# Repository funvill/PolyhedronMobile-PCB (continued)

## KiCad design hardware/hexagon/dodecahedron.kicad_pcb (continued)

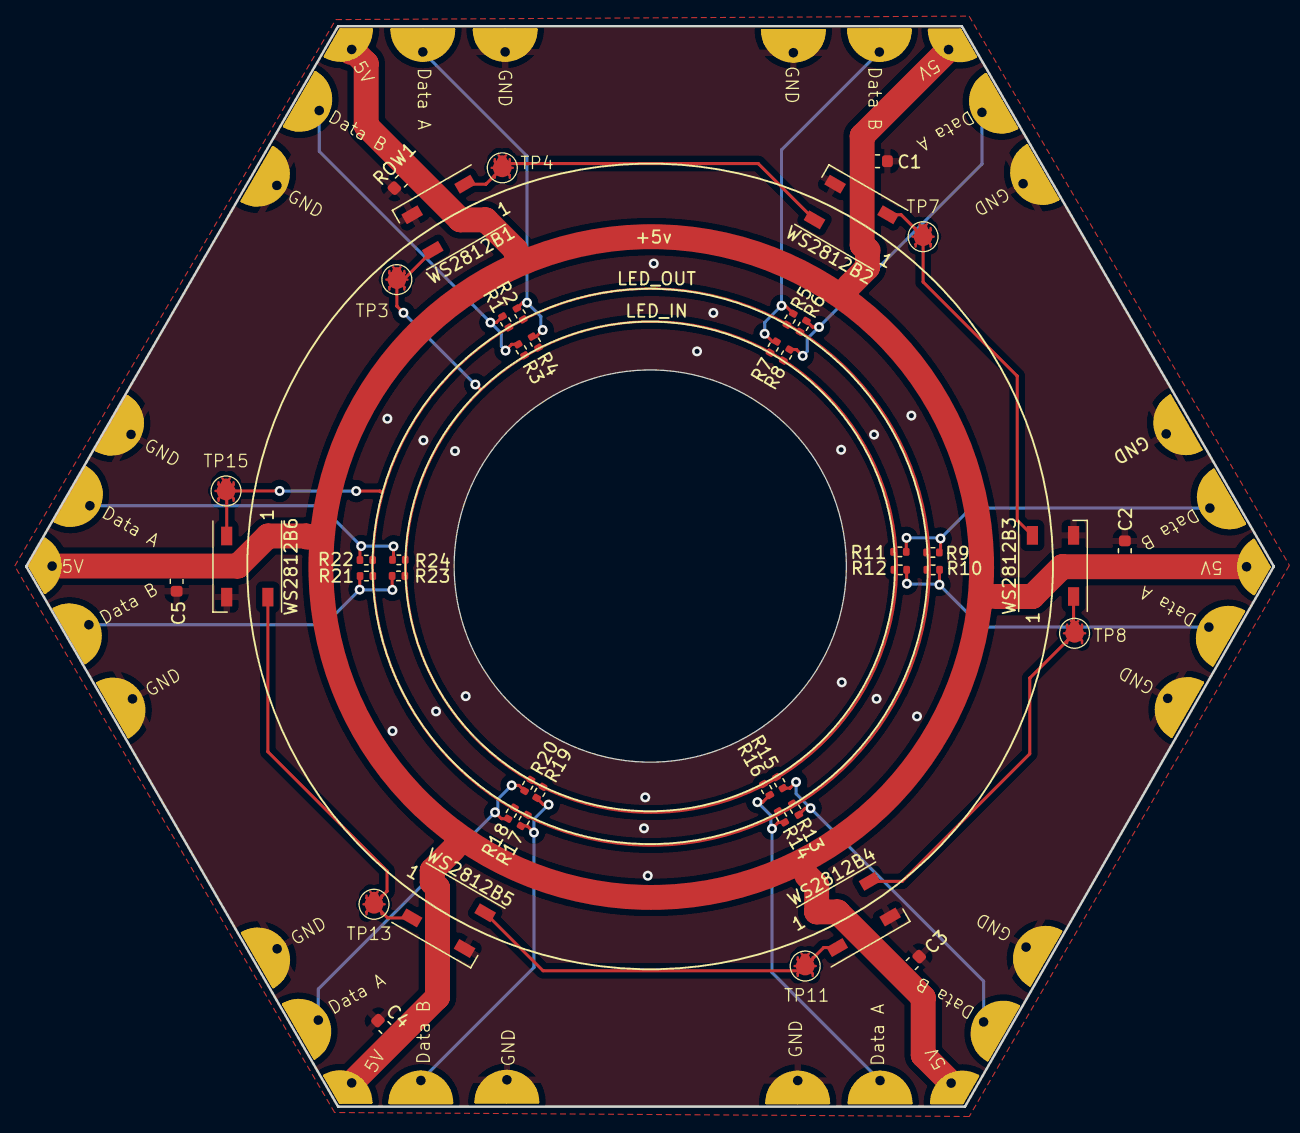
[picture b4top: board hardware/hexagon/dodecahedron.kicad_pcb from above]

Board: 2 copper layers, 100.0 x 86.6 mm, 49 parts (0 on the bottom side), 21 nets.

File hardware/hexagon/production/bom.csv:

Designator,Footprint,Quantity,Value,LCSC Part #
"C1, C2, C3, C4, C5",0603,5,"1uF,25V,X5R",C52923
"J1, J2, J3, J4, J5, J6",dodecahedron_corner,6,Conn_01x04,
"R1, R10, R11, R12, R13, R14, R15, R16, R17, R18, R19, R2, R20, R21, R22, R23, R24, R3, R4, R5, R6, R7, R8, R9",0402,24,0,C17168
ROW1,0603,1,"10uF,10V,X5R ",C52923
"TP11, TP13, TP15, TP3, TP4, TP7, TP8",SWS-Testpoint-Bug-SM-2.4mm,7,TestPoint,
"WS2812B1, WS2812B2, WS2812B3, WS2812B4, WS2812B5, WS2812B6",LED_WS2812B_PLCC4_5.0x5.0mm_P3.2mm,6,XL-5050RGBC-WS2812B,C2843785

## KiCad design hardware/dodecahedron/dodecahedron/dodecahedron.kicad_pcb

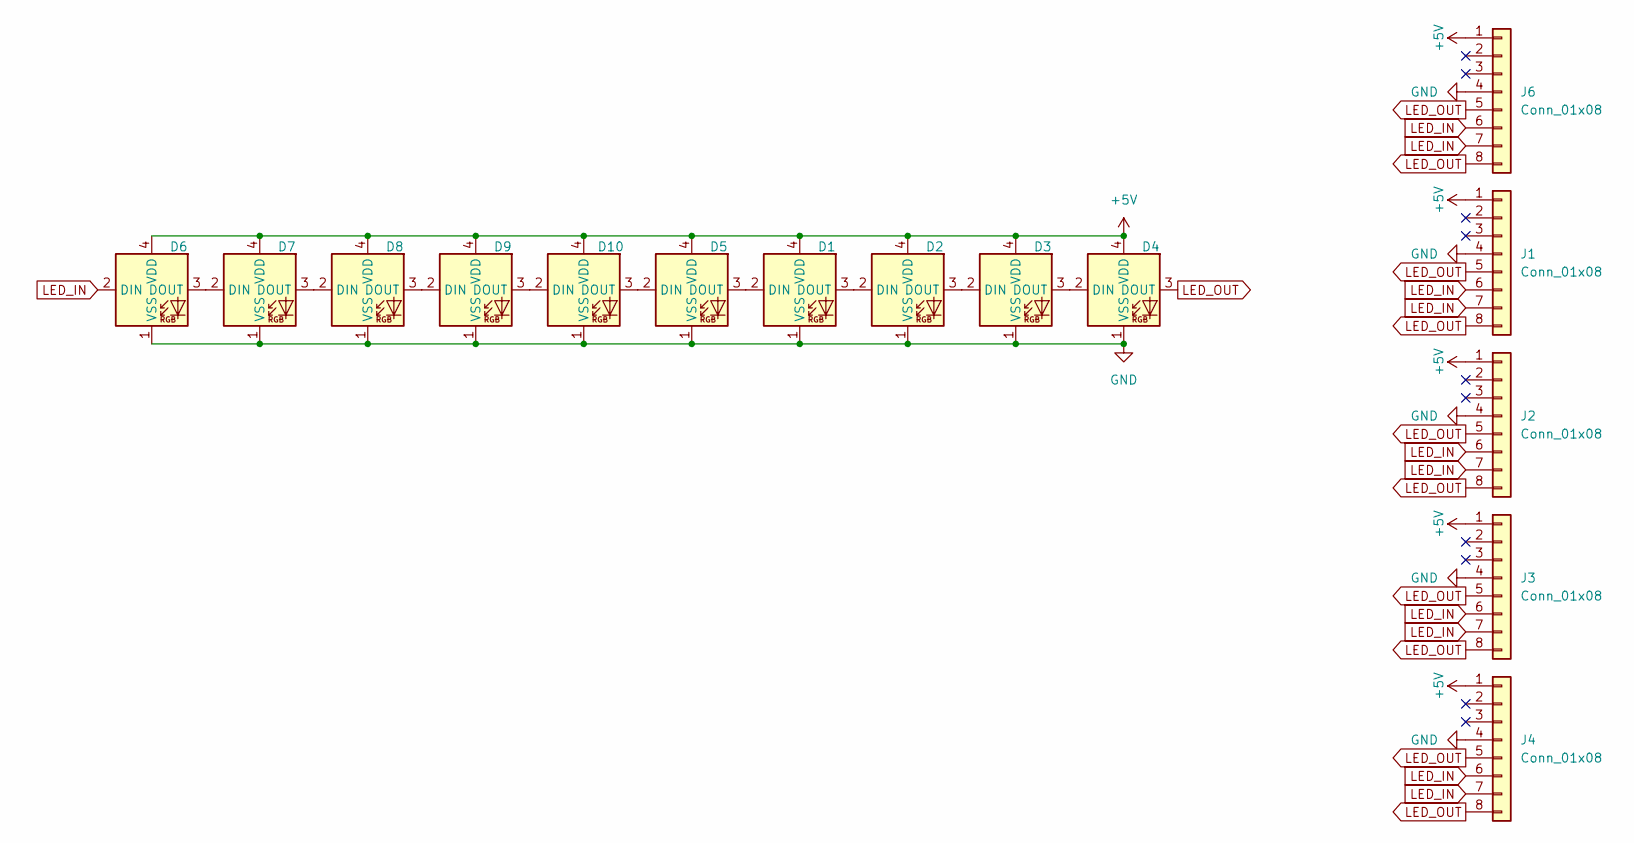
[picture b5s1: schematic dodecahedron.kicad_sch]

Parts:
D1, D2, D3, D4, D5, D6, D7, D8, D9, D10: LiteOn_LTST-E563C; LED_LiteOn_LTST-E563C_PLCC4_5.0x5.0mm_P3.2mm
J1, J2, J3, J4, J6: Conn_01x08; Pentagon-edge

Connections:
+5V: D1.4 (VDD), D2.4 (VDD), D3.4 (VDD), D4.4 (VDD), D5.4 (VDD), D6.4 (VDD), D7.4 (VDD), D8.4 (VDD), D9.4 (VDD), D10.4 (VDD), J1.1, J2.1, J3.1, J4.1, J6.1
GND: D1.1 (VSS), D2.1 (VSS), D3.1 (VSS), D4.1 (VSS), D5.1 (VSS), D6.1 (VSS), D7.1 (VSS), D8.1 (VSS), D9.1 (VSS), D10.1 (VSS), J1.4, J2.4, J3.4, J4.4, J6.4
LED_IN: D6.2 (DIN), J1.6, J1.7, J2.6, J2.7, J3.6, J3.7, J4.6, J4.7, J6.6, J6.7
LED_OUT: D4.3 (DOUT), J1.5, J1.8, J2.5, J2.8, J3.5, J3.8, J4.5, J4.8, J6.5, J6.8
unnamed: D1.2 (DIN), D5.3 (DOUT)
unnamed: D1.3 (DOUT), D2.2 (DIN)
unnamed: D2.3 (DOUT), D3.2 (DIN)
unnamed: D3.3 (DOUT), D4.2 (DIN)
unnamed: D6.3 (DOUT), D7.2 (DIN)
unnamed: D7.3 (DOUT), D8.2 (DIN)
unnamed: D8.3 (DOUT), D9.2 (DIN)
unnamed: D9.3 (DOUT), D10.2 (DIN)
unnamed: D5.2 (DIN), D10.3 (DOUT)

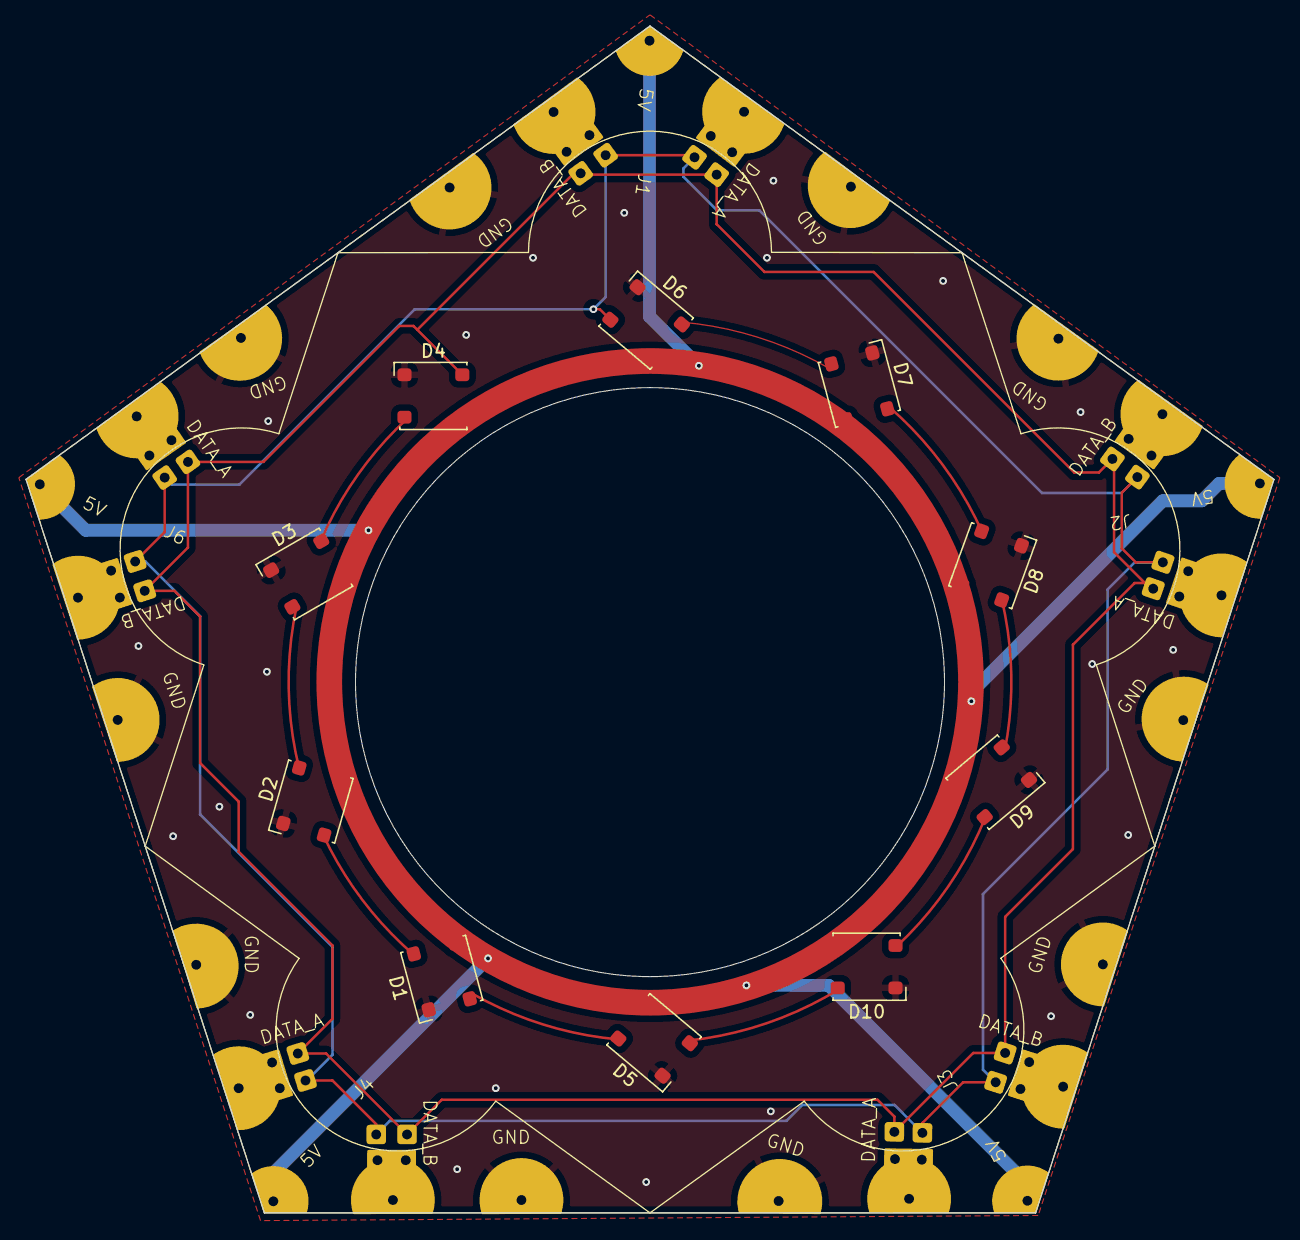
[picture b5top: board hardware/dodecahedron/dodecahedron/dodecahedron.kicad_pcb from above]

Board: 2 copper layers, 97.1 x 92.3 mm, 15 parts (0 on the bottom side), 13 nets.

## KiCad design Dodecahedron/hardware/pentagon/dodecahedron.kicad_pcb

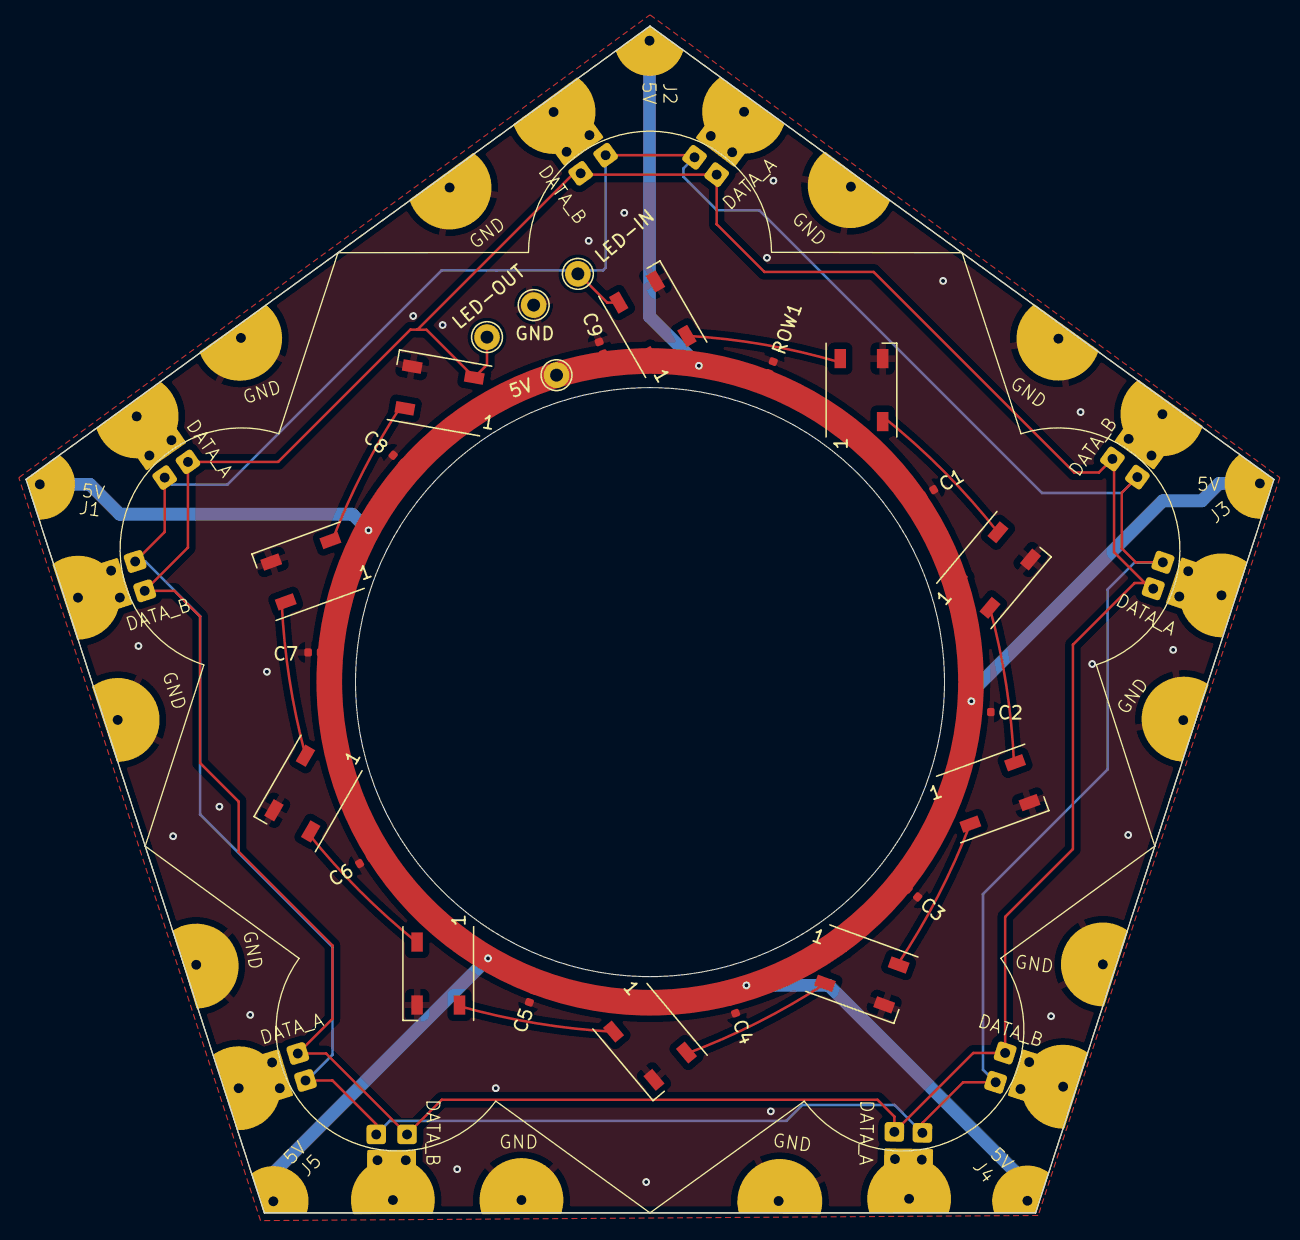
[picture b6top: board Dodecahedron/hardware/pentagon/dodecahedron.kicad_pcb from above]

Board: 2 copper layers, 97.1 x 92.3 mm, 29 parts (0 on the bottom side), 13 nets.

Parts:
5V: TestPoint; TestPoint_THTPad_D2.0mm_Drill1.0mm
C1, C2, C3, C4, C5, C6, C7, C8, C9: 1uF,25V,X5R; C_0402_1005Metric
GND: TestPoint; TestPoint_THTPad_D2.0mm_Drill1.0mm
J1, J2, J3, J4, J5: Conn_01x08; pentagon-corner
LED-IN: TestPoint; TestPoint_THTPad_D2.0mm_Drill1.0mm
LED-OUT: TestPoint; TestPoint_THTPad_D2.0mm_Drill1.0mm
ROW1: 10uF,10V,X5R; C_0402_1005Metric
WS2812B1, WS2812B2, WS2812B3, WS2812B4, WS2812B5, WS2812B6, WS2812B7, WS2812B8, WS2812B9, WS2812B10: XL-5050RGBC-WS2812B; LED_WS2812B_PLCC4_5.0x5.0mm_P3.2mm

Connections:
+5V: 5V.1, C1.1, C2.1, C3.1, C4.1, C5.1, C6.1, C7.1, C8.1, C9.1, J1.1, J2.1, J3.1, J4.1, J5.1, ROW1.2, WS2812B1.1 (VDD), WS2812B2.1 (VDD), WS2812B3.1 (VDD), WS2812B4.1 (VDD), WS2812B5.1 (VDD), WS2812B6.1 (VDD), WS2812B7.1 (VDD), WS2812B8.1 (VDD), WS2812B9.1 (VDD), WS2812B10.1 (VDD)
GND: C1.2, C2.2, C3.2, C4.2, C5.2, C6.2, C7.2, C8.2, C9.2, GND.1, J1.4, J2.4, J3.4, J4.4, J5.4, ROW1.1, WS2812B1.3 (GND), WS2812B2.3 (GND), WS2812B3.3 (GND), WS2812B4.3 (GND), WS2812B5.3 (GND), WS2812B6.3 (GND), WS2812B7.3 (GND), WS2812B8.3 (GND), WS2812B9.3 (GND), WS2812B10.3 (GND)
LED_IN: J1.6, J1.7, J2.6, J2.7, J3.6, J3.7, J4.6, J4.7, J5.6, J5.7, LED-IN.1, WS2812B1.4 (DIN)
LED_OUT: J1.5, J1.8, J2.5, J2.8, J3.5, J3.8, J4.5, J4.8, J5.5, J5.8, LED-OUT.1, WS2812B10.2 (DOU)
unnamed: WS2812B1.2 (DOU), WS2812B2.4 (DIN)
unnamed: WS2812B2.2 (DOU), WS2812B3.4 (DIN)
unnamed: WS2812B3.2 (DOU), WS2812B4.4 (DIN)
unnamed: WS2812B4.2 (DOU), WS2812B5.4 (DIN)
unnamed: WS2812B5.2 (DOU), WS2812B6.4 (DIN)
unnamed: WS2812B6.2 (DOU), WS2812B7.4 (DIN)
unnamed: WS2812B7.2 (DOU), WS2812B8.4 (DIN)
unnamed: WS2812B8.2 (DOU), WS2812B9.4 (DIN)
unnamed: WS2812B9.2 (DOU), WS2812B10.4 (DIN)

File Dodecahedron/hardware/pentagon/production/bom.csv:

Designator,Footprint,Quantity,Value,LCSC Part #
"5V, GND, LED-IN, LED-OUT",TestPoint_THTPad_D2.0mm_Drill1.0mm,4,TestPoint,
"C1, C2, C3, C4, C5, C6, C7, C8, C9",0402,9,"1uF,25V,X5R",C52923
"J1, J2, J3, J4, J5",pentagon-corner,5,Conn_01x08,
ROW1,0402,1,"10uF,10V,X5R ",C52923
"WS2812B1, WS2812B10, WS2812B2, WS2812B3, WS2812B4, WS2812B5, WS2812B6, WS2812B7, WS2812B8, WS2812B9",LED_WS2812B_PLCC4_5.0x5.0mm_P3.2mm,10,XL-5050RGBC-WS2812B,C2843785

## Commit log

2024-03-28 initial version
2024-03-28 Fixed up a rotated LED
2024-03-28 Added circles to the silk screen
2024-03-30 5 sided pentagram
2024-03-31 Separated it into three projects. finished hexagon
2024-03-31 Added production files and readme
2024-03-31 Added Hexagon production, as sent to JLCPCB
2024-03-31 Added more images and updated the readme.md file with links
2024-06-04 WIP for v2 of tetragonal Deltohedron
2024-06-05 Adding all the components to the PCB
2024-11-16 TetragonalTrapezohedron + PentagrammicDipyramid + Dodecahedron
2024-11-16 WIP PentagrammicDipyramid
2024-12-03 RhombicDodecahedron
2024-12-03 Added more images to readme
